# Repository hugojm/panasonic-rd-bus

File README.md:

# panasonic-rd-bus

Local Home Assistant control for Panasonic **residential ducted** air conditioners that only
have a 2-wire wired controller (terminals **R1/R2**, CZ-RD514C family). These units have no
CN-CNT port, so the usual Panasonic ESPHome projects don't apply. An ESP32 joins the R1/R2
bus as a **second wall controller**: it reads the unit's real state and sends the same
commands the wall controller does. No cloud, no IR, no button pressing.

**Status:** working on a Panasonic **W18BD3P** with a **CZ-RD514C** controller (Spain,
2026-11). Power, mode, fan, setpoint and the filter warning work from Home Assistant, and
changes made at the wall controller show up in Home Assistant too. It is tested on **one
unit**; if you try it on another, please open an issue with your model and a capture.

> Have a PACi (commercial) unit with a CZ-RTC controller instead? Use
> [rndm2/esphome_panasonic_paci](https://github.com/rndm2/esphome_panasonic_paci) with a
> CZ-CAPWFC1 bridge. That is a different protocol.

The story of how it was decoded: [docs/writeup.md](docs/writeup.md).

## How the bus works (short version)

- 2 wires, ~15 V DC. A device talks by pulling the line down with a **~19 kHz carrier**
  for each 0-bit; silence is a 1-bit. **2 ms per bit, 8E1** (~495 baud).
- The bus polls `80 81 90…9F` every 154.6 ms. The wall controller answers poll `80`;
  poll `81` (a second controller) is free, so the ESP32 answers there, 44 ms after it.
- Frames are `E3|E1 LEN payload CS` with `sum & 0x7F == 0`. `E3` = wall controller,
  `E1` = indoor unit.
- Registers: `60` power, `61` mode, `62` fan, `64` setpoint (°C = value + 16), `66` filter.

Full details, timings and unknowns: [docs/protocol.md](docs/protocol.md).

## Hardware

Three ways to build the interface. All share the same proven circuit
([docs/hardware.md](docs/hardware.md)): one NPN transistor + 10k/680 Ω divider to receive,
one NPN transistor + 220 Ω to transmit.

| Option | What | State |
| --- | --- | --- |
| Breadboard | ESP32 DevKit, 2 × 2N2222, 6 resistors | working (this is what runs today) |
| [PCB v1](hardware/pcb/) | 60 × 46 mm, ESP32-C3 module, USB-C powered, factory-assembled at JLCPCB | ordered, boards on the way |
| [PCB v2](hardware/pcb_v2/) | same, but powered from the AC bus itself (~19 mA, current-limited) | design, not built yet |
| [PCB v3](hardware/pcb_v3/) | same as v1, but **isolated**: optocouplers + isolated DC-DC, the ESP32 never shares a wire with the bus | design, not built yet |

> ⚠️ **v2 and v3 are untested designs.** They pass KiCad's design checks, but no board has
> been built or tried on a real AC yet. Don't order them expecting them to work; use the
> breadboard circuit or v1. Results will be posted here once they're tested.

The board files are generated by a Python script against KiCad 10's API (`build_pcb.py`),
checked with KiCad's DRC, and come with JLCPCB-ready Gerber/BOM/CPL files.

## Software

| Path | What |
| --- | --- |
| `esphome/components/panasonic_rd/` | ESPHome climate component (receive, transmit, filter sensor) |
| `esphome/panasonic-ac.yaml` | config for an ESP32 DevKit on a breadboard (RX GPIO26, TX GPIO25) |
| `esphome/panasonic-ac-c3.yaml` | config for PCB v1 |
| `esphome/panasonic-ac-v2.yaml` | config for PCB v2 (holds Wi-Fi off until the bus supply is charged) |
| `esphome/components/panasonic_rd/rdbus.h` | protocol core, no platform dependencies: carrier envelope, 8E1 decoding, frames, reply-slot timing |
| `firmware/` | PlatformIO serial sniffer for mapping a new unit (markers, stats, armed transmit) |
| `tools/decode_capture.py` | decode PulseView/sigrok CSV captures with the same algorithm |
| `test/` | native tests: `make -C test` |

### Quick start (breadboard)

1. Build the circuit in [docs/hardware.md](docs/hardware.md) and read its safety notes first.
2. Create `esphome/secrets.yaml` with `wifi_ssid`, `wifi_password`, `api_key`,
   `ota_password` and `ap_password`.
3. Flash:
   ```bash
   cd esphome
   esphome run panasonic-ac.yaml
   ```
4. Add the device in Home Assistant (Settings → Devices → ESPHome). You get a climate
   entity, a "Filter needs cleaning" sensor and a "Reset filter warning" button.

The register values in the YAML are the ones confirmed on a W18BD3P. Another model may
differ: map yours with the sniffer first ([docs/test-plan.md](docs/test-plan.md)).

## Safety and disclaimer

- **Switch the AC off at the breaker** before touching its wiring. On many indoor units the
  R1/R2 terminals sit next to mains terminals.
- The simple circuit is **not isolated**: the ESP32's ground is bus −. Find which wire is +
  with a multimeter first. Never let bus voltage (15 V) reach a GPIO directly; it will
  destroy the pin.
- This is an independent hobby project, not affiliated with or endorsed by Panasonic. Adding
  a device to your AC's control bus may affect your warranty. You do this at your own risk.

## Credits

Built on the work in the Home Assistant community thread
[Panasonic PACi / commercial unit wired controller protocol](https://community.home-assistant.io/t/panasonic-paci-commercial-unit-wired-controller-protocol-2-wire-bus-anyone-working-on-this/996275),
especially the captures and frame analysis shared there.

## License

Software: [MIT](LICENSE). Hardware (`hardware/`): [CERN-OHL-P-2.0](hardware/LICENSE).

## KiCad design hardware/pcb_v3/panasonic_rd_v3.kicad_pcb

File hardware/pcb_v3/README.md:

# AC board v3: isolated from the AC bus (draft, not ordered)

> ⚠️ **Untested design.** It passes KiCad's design checks and the isolation-gap check, but no
> v3 board has been built or connected to an AC yet. The optocoupler timing is calculated,
> not measured. Use it at your own risk, or wait for test results.

Same ESP32-C3 board as [v1](../pcb/README.md), but the ESP32 never shares a wire with the AC
bus. Signals cross a 2 mm gap in the copper through two optocouplers, and the bus-side
transmit stage gets its power from a small isolated DC-DC. Wiring it wrong, a laptop on USB,
or a fault on the AC side can't reach the ESP32. 60 × 54 mm (8 mm taller than v1).

**Status (2026-11-22):** designed. KiCad DRC 0 errors / 0 unconnected, and
`check_isolation.py` reports no bus/ESP32 copper closer than 2 mm except the DC-DC's own pins.
Not built or tested. The firmware is unchanged: `esphome/panasonic-ac-c3.yaml` (RX GPIO4,
TX GPIO5, same polarity as v1).

## Circuit

```
            ESP32 side (GND)                 ║          bus side (BGND = BUS-, floating)
                                             ║
 RX (GPIO4) ── U5 H11L1 out ── 4.7k ── 3V3   ║  U5 LED ── 7.5 V zener ── 2k ── BUS+ (+ ROJO)
                                             ║     └── BUS- (- MARRON)
 TX (GPIO5) ── 680 ── U6 H11L1 LED ── GND    ║  U6 out ──┬── 10k ── V5I
                                             ║           └── 4.7k ── MMBT3906 ── 1k ── MMBT2222A ── 220 ── BUS+
 USB 5V ── B0505S-1WR3 (pins 1-2) ═══════════╬══ (pins 3-4) ── V5I (isolated 5 V) / BGND
```

- **Receive.** The U5 LED conducts only while BUS+ is above ~11 V (7.5 V zener + LED + 2k).
  Idle (15.2 V) = LED on = RX low; carrier dips (7.6 V) = RX high. That is the same polarity
  as v1's transistor, so the decoder needs no change. Bus load: ~3 mA at idle.
- **Transmit.** TX high lights U6. Its output goes low, which turns on the PNP (Q5), the NPN
  (Q6) and pulls BUS+ down through 220 Ω, like v1 and the breadboard. ESP32 off or idle:
  U6 dark, output pulled high, Q5/Q6 off, the bus is left alone.
- **Isolated supply.** The B0505S takes 5 V from USB and makes a floating 5 V (V5I) for U6
  and Q5 on the bus side, so the transmit stage draws nothing from the AC bus.
- **Not polarity-proof.** Red to `+ ROJO`, brown to `- MARRON`, as on v1. Reversed, nothing
  works, but the ESP32 side is still protected.

The isolation is functional (low voltages, keeps the two grounds apart), not a mains safety
barrier: the DC-DC's input and output pins are 2.54 mm apart, which is the module's own
pitch. The B0505S itself is rated 1.5 kV.

## Parts new in v3 (in stock 2026-11-22)

| Part | LCSC | Notes |
| --- | --- | --- |
| H11L1S(TA) ×2 | C78589 | Schmitt-trigger optocoupler, 1.6 mA LED, fast enough for 19 kHz (a PC817 isn't) |
| B0505S-1WR3 | C7465178 | 1 W isolated DC-DC, SIP-4 through-hole: JLCPCB hand-solders it |
| BZT52C7V5 | C707137 | 7.5 V zener |
| MMBT3906 | C7420354 | PNP |
| 220 Ω 0805 | C17557 | bigger than v1's 0603: it carries ~60 mA in bursts |

Removed from v1: Q1/Q2 and their resistors.

## Before ordering

- Order only after v1 works, and test v3 on the real bus first: the optocouplers' switching
  time and the ~3 mA receive load are calculated, not measured.
- In JLCPCB's placement viewer, check the new parts: **U5/U6** (pin 1 = LED anode; U5's LED
  row faces the screw terminal, U6's faces the module), **Q5/Q6**, **DZ1** (stripe/cathode
  toward the 2k resistor). The B0505S uses a generic 4-pin 2.54 mm footprint. The silkscreen
  box shows its body and pin 1 (the pin nearest the right-hand edge).
- Rebuild with `./make_fab.sh`; re-check isolation with KiCad's Python: `python3 check_isolation.py 2.0`.

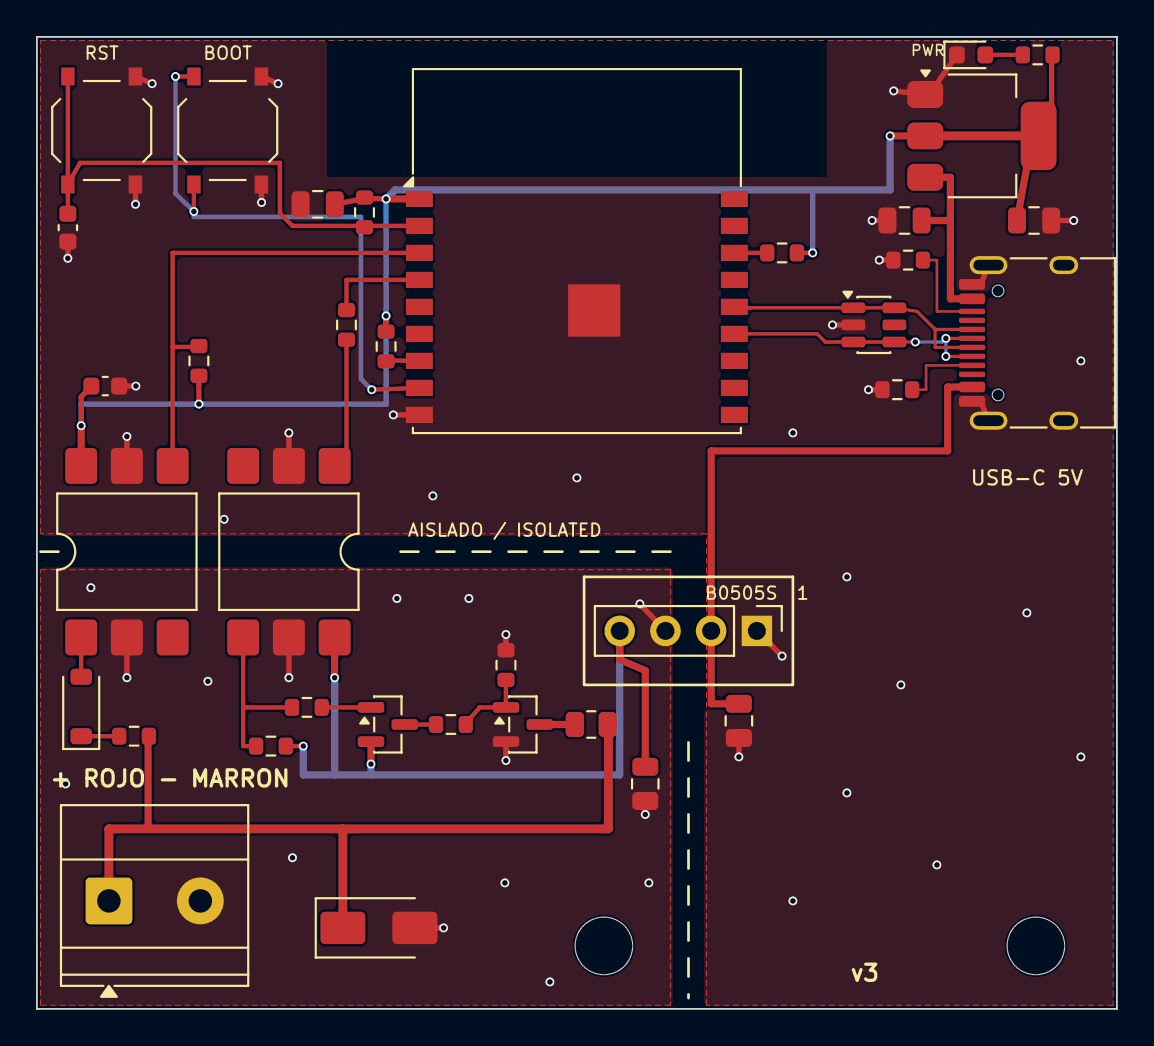
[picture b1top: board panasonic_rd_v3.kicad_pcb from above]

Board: 2 copper layers, 60.0 x 54.0 mm, 38 parts (0 on the bottom side), 26 nets.

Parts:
C1, C2, C4, C24, C25: 10uF; C_0805_2012Metric
C5: 1uF; C_0603_1608Metric
C23: 100nF; C_0603_1608Metric
D1: SMAJ24A; D_SMA
D2: LED; LED_0603_1608Metric
DZ1: BZT52C7V5; D_SOD-123
H1, H2: MountingHole_3.2mm_M3
J1: TYPE-C-31-M-12; USB_C_Receptacle_HRO_TYPE-C-31-M-12
J2: KF301-5.0-2P; TerminalBlock_Phoenix_MKDS-1,5-2-5.08_1x02_P5.08mm_Horizont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
PS1: B0505S-1WR3; PinHeader_1x04_P2.54mm_Vertical
Q5: MMBT3906; SOT-23
Q6: MMBT2222A; SOT-23
R7, R9, R10, R33, R35: 10k; R_0603_1608Metric
R11, R12: 5.1k; R_0603_1608Metric
R13, R34: 1k; R_0603_1608Metric
R30: 2k; R_0603_1608Metric
R31: 220; R_0805_2012Metric
R32, R37: 4.7k; R_0603_1608Metric
R38: 680; R_0603_1608Metric
SW1: RESET; SW_Push_1P1T_XKB_TS-1187A
SW2: BOOT; SW_Push_1P1T_XKB_TS-1187A
U1: ESP32-C3-WROOM-02-N4; ESP32-C3-WROOM-02
U2: USBLC6-2SC6; SOT-23-6
U3: AMS1117-3.3; SOT-223-3_TabPin2
U5, U6: H11L1S; SMDIP-6_W9.53mm

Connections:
+3V3: C2.1, C4.2, C23.1, R7.2, R9.2, R10.2, R13.2, R37.1, U1.1, U3.2, U5.6
BGND: C24.1, D1.2, J2.2, PS1.3, Q6.2, R35.2, U5.2, U6.5
BUS_P: D1.1, J2.1, R30.2, R31.2
CC1: J1.A5, R11.2
CC2: J1.B5, R12.2
EN: C5.2, R7.1, SW1.1, U1.2
GND: C1.1, C2.2, C4.1, C5.1, C23.2, C25.1, D2.1, J1.A1, J1.A12, J1.B1, J1.B12, J1.SH, PS1.1, R11.1, R12.1, SW1.2, SW2.2, U1.9, U1.19, U2.2, U3.1, U5.5, U6.2
IO2: R10.1, U1.16
IO8: R9.1, U1.7
IO9: SW2.1, U1.8
LED_A: D2.2, R13.1
Q5_B: Q5.1, R32.2
Q5_C: Q5.3, R34.1
Q6_B: Q6.1, R34.2, R35.1
Q6_C: Q6.3, R31.1
RX: R37.2, U1.3, U5.4
RX_A: DZ1.2, U5.1
RX_K: DZ1.1, R30.1
TX: R38.2, U1.4
TX_A: R38.1, U6.1
TX_O: R32.1, R33.1, U6.4
USB_DN: J1.A7, J1.B7, U1.13, U2.3, U2.4
USB_DP: J1.A6, J1.B6, U1.14, U2.1, U2.6
V5I: C24.2, PS1.4, Q5.2, R33.2, U6.6
VBUS: C1.2, J1.A9, J1.B4, U3.3
VBUS2: C25.2, J1.A4, J1.B9, PS1.2

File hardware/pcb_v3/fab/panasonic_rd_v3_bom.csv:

Comment,Designator,Footprint,LCSC Part #
LED,D2,LED_0603_1608Metric,C2286
H11L1S,"U5,U6",SMDIP-6_W9.53mm,C78589
10k,"R7,R9,R10,R33,R35",R_0603_1608Metric,C25804
ESP32-C3-WROOM-02-N4,U1,ESP32-C3-WROOM-02,C2934560
10uF,"C1,C2,C4,C24,C25",C_0805_2012Metric,C15850
5.1k,"R11,R12",R_0603_1608Metric,C23186
4.7k,"R32,R37",R_0603_1608Metric,C23162
220,R31,R_0805_2012Metric,C17557
RESET/BOOT,"SW1,SW2",SW_Push_1P1T_XKB_TS-1187A,C318884
BZT52C7V5,DZ1,D_SOD-123,C707137
680,R38,R_0603_1608Metric,C23228
USBLC6-2SC6,U2,SOT-23-6,C7519
B0505S-1WR3,PS1,PinHeader_1x04_P2.54mm_Vertical,C7465178
1uF,C5,C_0603_1608Metric,C15849
100nF,C23,C_0603_1608Metric,C14663
MMBT3906,Q5,SOT-23,C7420354
1k,"R13,R34",R_0603_1608Metric,C21190
MMBT2222A,Q6,SOT-23,C8512
TYPE-C-31-M-12,J1,USB_C_Receptacle_HRO_TYPE-C-31-M-12,C165948
SMAJ24A,D1,D_SMA,C90510
2k,R30,R_0603_1608Metric,C22975
AMS1117-3.3,U3,SOT-223-3_TabPin2,C6186
KF301-5.0-2P,J2,"TerminalBlock_Phoenix_MKDS-1,5-2-5.08_1x02_P5.08mm_Horizontal",C474881

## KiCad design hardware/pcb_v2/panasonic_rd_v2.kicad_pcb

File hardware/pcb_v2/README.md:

# AC board v2: powered from the AC bus (draft, not ordered)

> ⚠️ **Untested design.** It passes KiCad's design checks, but no v2 board has been built or
> connected to an AC yet. The bus's ability to power it is still unmeasured. Use it at your
> own risk, or wait for test results.

Same 60 × 46 mm board as [v1](../pcb/README.md), but no USB charger needed: it takes its
power from the two bus wires it already listens on. USB-C stays for flashing and as a
backup supply.

**Status (2026-11-22):** designed, KiCad DRC 0 errors / 0 unconnected, firmware
`esphome/panasonic-ac-v2.yaml` compiles. Not built yet. Order it only after v1 works
and the bus current is measured (below).

## How the power works

```
BUS+ ─ D3 SS14 ─ Q3 PZT2222A ─ R21 33 Ω ─┬─ VSTORE: C10 + C11, 2 × 1000 µF ─ U4 TPS560430X ─ L1 10 µH ─ 3.3 V
                   R20 4.7k │  Q4 MMBT2222A┘   (≤ 13.7 V)                     EN: R24 56k / R25 10k
USB VBUS2 ─ D4 SS14 ───────────────────────────┘                             USB: D5 SS14 + R26 10k → EN
```

- **Current limiter.** Q4 turns Q3 down when 33 Ω carries 0.65 V, so the board never
  draws more than **~19 mA** from the bus, whatever the ESP32 does. A steady draw is
  invisible to the 19 kHz signal; the Wi-Fi bursts (~300 mA) come out of VSTORE.
  To change the budget, change R21: 47 Ω ≈ 14 mA, 33 Ω ≈ 19 mA, 27 Ω ≈ 24 mA.
- **D3** stops VSTORE feeding back into the bus when the line is pulled low.
- **Start-up.** U4 only switches on when VSTORE reaches ~8.1 V (EN divider, TPS560430
  threshold 1.23 V) and stops at ~7.3 V, so the ESP32 never boots on a half-charged
  supply. Charging 2 mF to 8 V at 19 mA takes under a second.
- **Wi-Fi gate.** VSTORE / 6.56 goes to IO3. The firmware turns Wi-Fi on only above
  11.5 V (or below 6.5 V, which only happens on USB), turns it off again if VSTORE
  sags to 8 V, and uses Wi-Fi power-save. "Bus supply voltage" shows up in Home
  Assistant as a diagnostic sensor.
- **USB only.** VBUS2 (the connector's A4/B9 pins) feeds VSTORE through D4 (~4.6 V)
  and forces EN on through D5 + R26. The TPS560430 runs from 4 V.
- Gone from v1: the AMS1117 regulator (U3).

## Before ordering: measure the bus budget

1. AC breaker off. Put the multimeter (mA range) in series with one wall-controller wire.
   Breaker on, read the current. That is what the bus already gives one controller.
2. With v1 running, confirm VSTORE math against reality: bus voltage at the terminal
   with the AC idle and while the board transmits.
3. If the controller draws well under 19 mA, raise R21 to 47 Ω (≈14 mA) before ordering.

## Ordering

Same steps as v1 (`fab/panasonic_rd_v2_gerbers.zip`, `_bom.csv`, `_cpl.csv`; Economic,
top side, Confirm Parts Placement). In the placement viewer check the new parts first,
because the rotation fixes in `bom_cpl.py` were confirmed only for v1's parts:
**U4** (TPS560430, SOT-23-6: pin 1 at the ▼ mark), **Q3** (PZT2222A: tab on the left,
on the big pad), **D3–D5** (stripe = cathode, toward Q3 / down), **C10/C11** (+ sides
facing each other in the middle), **L1**.

New parts (all in stock 2026-11-22): TPS560430XDBVR C524782, PZT2222A C189428,
SS14 C2909920, CKCS5040 10 µH C354610, 1000 µF 25 V 10×10.5 C51018391; the rest are
JLCPCB basic resistors/capacitors. Expect about the same price as v1, plus ~$15 of
extended-part fees.

## Risks

- The bus supply's real capacity is unknown. If ~19 mA upsets the indoor unit (error
  code or garbled frames), lower the current (R21) or power from USB: the board works
  the same with a charger.
- First connection to Wi-Fi is the costliest moment. If it keeps cycling on/off, see the
  "VSTORE … Wi-Fi off" log lines and lower `output_power` or raise R21's budget.
- Rebuild: `./make_fab.sh` (same KiCad 10 setup as v1).

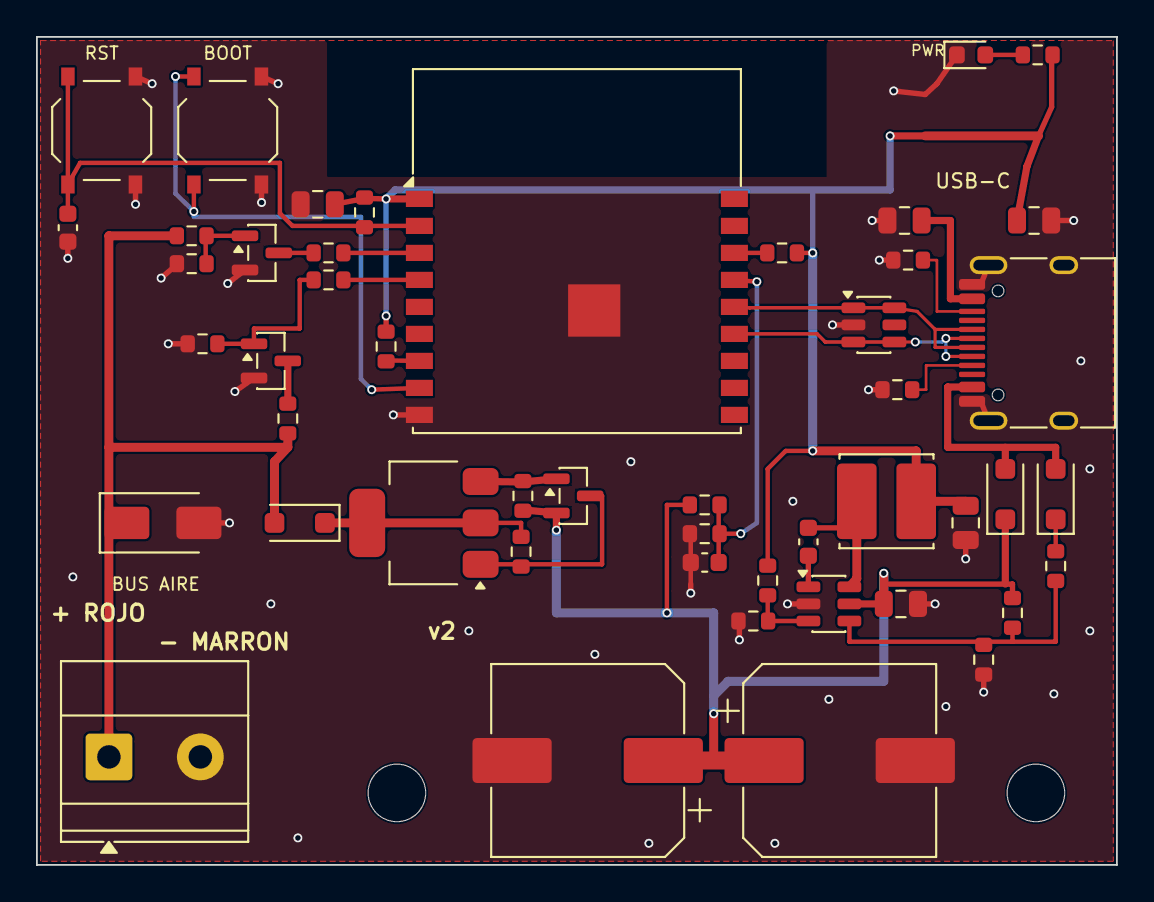
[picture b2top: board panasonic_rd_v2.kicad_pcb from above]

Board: 2 copper layers, 60.0 x 46.0 mm, 50 parts (0 on the bottom side), 30 nets.

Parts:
C1, C2, C4: 10uF; C_0805_2012Metric
C5: 1uF; C_0603_1608Metric
C10, C11: 1000uF 25V; CP_Elec_10x10.5
C12: 10uF 25V; C_0805_2012Metric
C13, C15: 100nF; C_0603_1608Metric
C14: 22uF; C_0805_2012Metric
D1: SMAJ24A; D_SMA
D2: LED; LED_0603_1608Metric
D3, D4, D5: SS14; D_SOD-123F
H1, H2: MountingHole_3.2mm_M3
J1: TYPE-C-31-M-12; USB_C_Receptacle_HRO_TYPE-C-31-M-12
J2: KF301-5.0-2P; TerminalBlock_Phoenix_MKDS-1,5-2-5.08_1x02_P5.08mm_Horizont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
L1: 10uH; L_Cenker_CKCS5040
Q1, Q2, Q4: MMBT2222A; SOT-23
Q3: PZT2222A; SOT-223-3_TabPin2
R1, R5, R7, R9, R10, R25, R26: 10k; R_0603_1608Metric
R2: 680; R_0603_1608Metric
R3, R4, R13: 1k; R_0603_1608Metric
R6: 220; R_0603_1608Metric
R11, R12: 5.1k; R_0603_1608Metric
R20: 4.7k; R_0603_1608Metric
R21: 33; R_0603_1608Metric
R22: 51k; R_0603_1608Metric
R23: 22k; R_0603_1608Metric
R24: 56k; R_0603_1608Metric
R27: 100k; R_0603_1608Metric
R28: 18k; R_0603_1608Metric
SW1: RESET; SW_Push_1P1T_XKB_TS-1187A
SW2: BOOT; SW_Push_1P1T_XKB_TS-1187A
U1: ESP32-C3-WROOM-02-N4; ESP32-C3-WROOM-02
U2: USBLC6-2SC6; SOT-23-6
U4: TPS560430XDBVR; SOT-23-6

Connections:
+3V3: C2.1, C4.2, C14.2, L1.2, R7.2, R9.2, R10.2, R13.2, R22.2, U1.1
ADC: C15.2, R27.2, R28.2, U1.15
BUCK_EN: R24.1, R25.2, R26.1, U4.4
BUS_D: D3.1, Q3.2, R20.2
BUS_P: D1.1, D3.2, J2.1, R1.1, R6.1
CB: C13.1, U4.1
CC1: J1.A5, R11.2
CC2: J1.B5, R12.2
CS_E: Q3.3, Q4.1, R21.2
EN: C5.2, R7.1, SW1.1, U1.2
EN_USB: D5.1, R26.2
FB: R22.1, R23.2, U4.3
GND: C1.1, C2.2, C4.1, C5.1, C10.2, C11.2, C12.2, C14.1, C15.1, D1.2, D2.1, J1.A1, J1.A12, J1.B1, J1.B12, J1.SH, J2.2, Q1.2, Q2.2, R2.1, R5.1, R11.1, R12.1, R23.1, R25.1, R28.1, SW1.2, SW2.2, U1.9, U1.19, U2.2, U4.2
IO2: R10.1, U1.16
IO8: R9.1, U1.7
IO9: SW2.1, U1.8
LED_A: D2.2, R13.1
Q1_B: Q1.1, R1.2, R2.2
Q1_C: Q1.3, R3.1
Q2_B: Q2.1, R4.1, R5.2
Q2_C: Q2.3, R6.2
Q3_B: Q3.1, Q4.3, R20.1
RX: R3.2, U1.3
SW: C13.2, L1.1, U4.6
TX: R4.2, U1.4
USB_DN: J1.A7, J1.B7, U1.13, U2.3, U2.4
USB_DP: J1.A6, J1.B6, U1.14, U2.1, U2.6
VBUS: C1.2, J1.A9, J1.B4
VBUS2: D4.2, D5.2, J1.A4, J1.B9
VSTORE: C10.1, C11.1, C12.1, D4.1, Q4.2, R21.1, R24.2, R27.1, U4.5

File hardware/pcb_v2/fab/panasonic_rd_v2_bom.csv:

Comment,Designator,Footprint,LCSC Part #
PZT2222A,Q3,SOT-223-3_TabPin2,C189428
1k,"R3,R4,R13",R_0603_1608Metric,C21190
22uF,C14,C_0805_2012Metric,C45783
22k,R23,R_0603_1608Metric,C31850
KF301-5.0-2P,J2,"TerminalBlock_Phoenix_MKDS-1,5-2-5.08_1x02_P5.08mm_Horizontal",C474881
10k,"R1,R5,R7,R9,R10,R25,R26",R_0603_1608Metric,C25804
10uF/10uF 25V,"C1,C2,C4,C12",C_0805_2012Metric,C15850
SMAJ24A,D1,D_SMA,C90510
MMBT2222A,"Q1,Q2,Q4",SOT-23,C8512
TPS560430XDBVR,U4,SOT-23-6,C524782
18k,R28,R_0603_1608Metric,C25810
RESET/BOOT,"SW1,SW2",SW_Push_1P1T_XKB_TS-1187A,C318884
100nF,"C13,C15",C_0603_1608Metric,C14663
SS14,"D3,D4,D5",D_SOD-123F,C2909920
10uH,L1,L_Cenker_CKCS5040,C354610
100k,R27,R_0603_1608Metric,C25803
4.7k,R20,R_0603_1608Metric,C23162
680,R2,R_0603_1608Metric,C23228
33,R21,R_0603_1608Metric,C23140
1000uF 25V,"C10,C11",CP_Elec_10x10.5,C51018391
ESP32-C3-WROOM-02-N4,U1,ESP32-C3-WROOM-02,C2934560
56k,R24,R_0603_1608Metric,C23206
TYPE-C-31-M-12,J1,USB_C_Receptacle_HRO_TYPE-C-31-M-12,C165948
USBLC6-2SC6,U2,SOT-23-6,C7519
5.1k,"R11,R12",R_0603_1608Metric,C23186
1uF,C5,C_0603_1608Metric,C15849
LED,D2,LED_0603_1608Metric,C2286
220,R6,R_0603_1608Metric,C22962
51k,R22,R_0603_1608Metric,C23196

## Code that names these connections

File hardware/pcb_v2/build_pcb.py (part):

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track('USB_DN', [(48.8, 16.95), (47.64, 16.95)], W['USB'])
track('USB_DP', [(45.36, 15.05), (39.6, 15.05), (38.75, 15.0)], 0.2)
track('USB_DN', [(45.36, 16.95), (43.8, 16.95), (43.35, 16.5), (38.75, 16.5)], 0.2)
track('USB_DP', [(47.64, 15.05), (45.36, 15.05)], 0.2)   # USBLC6 pass-through (pins 6-1)
track('USB_DN', [(47.64, 16.95), (45.36, 16.95)], 0.2)   # (pins 4-3)
track('GND', [(52.5, 13.6), (52.87, 12.68)], 0.3)       # USB-C GND pads to the shield
track('GND', [(52.5, 20.4), (52.87, 21.32)], 0.3)
track('CC2', [(51.95, 15.25), (50.0, 15.25), (50.0, 12.4), (49.175, 12.4)], W['CC'])
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P = 0.5   # bus/storage width
# BUS+ -> D3 anode; D3 cathode -> PZT2222A collector tab
track('BUS_P', [(13.94, 22.8), (13.2, 23.6), (13.2, 27.0)], P)
track('BUS_D', [(16.0, 27.0), (18.35, 27.0), (24.65, 27.0)], P)   # tab and pin 2 are both the collector
# collector pin -> bias resistor R20 -> base; Q4 collector also pulls the base
track('BUS_D', [(24.65, 27.0), (26.9, 27.0), (26.9, 27.825)], W['SIG'])
track('Q3_B', [(24.65, 29.3), (26.9, 29.3), (26.9, 29.375)], W['SIG'])
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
